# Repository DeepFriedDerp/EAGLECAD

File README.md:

# EAGLECAD
a place for my eagle files

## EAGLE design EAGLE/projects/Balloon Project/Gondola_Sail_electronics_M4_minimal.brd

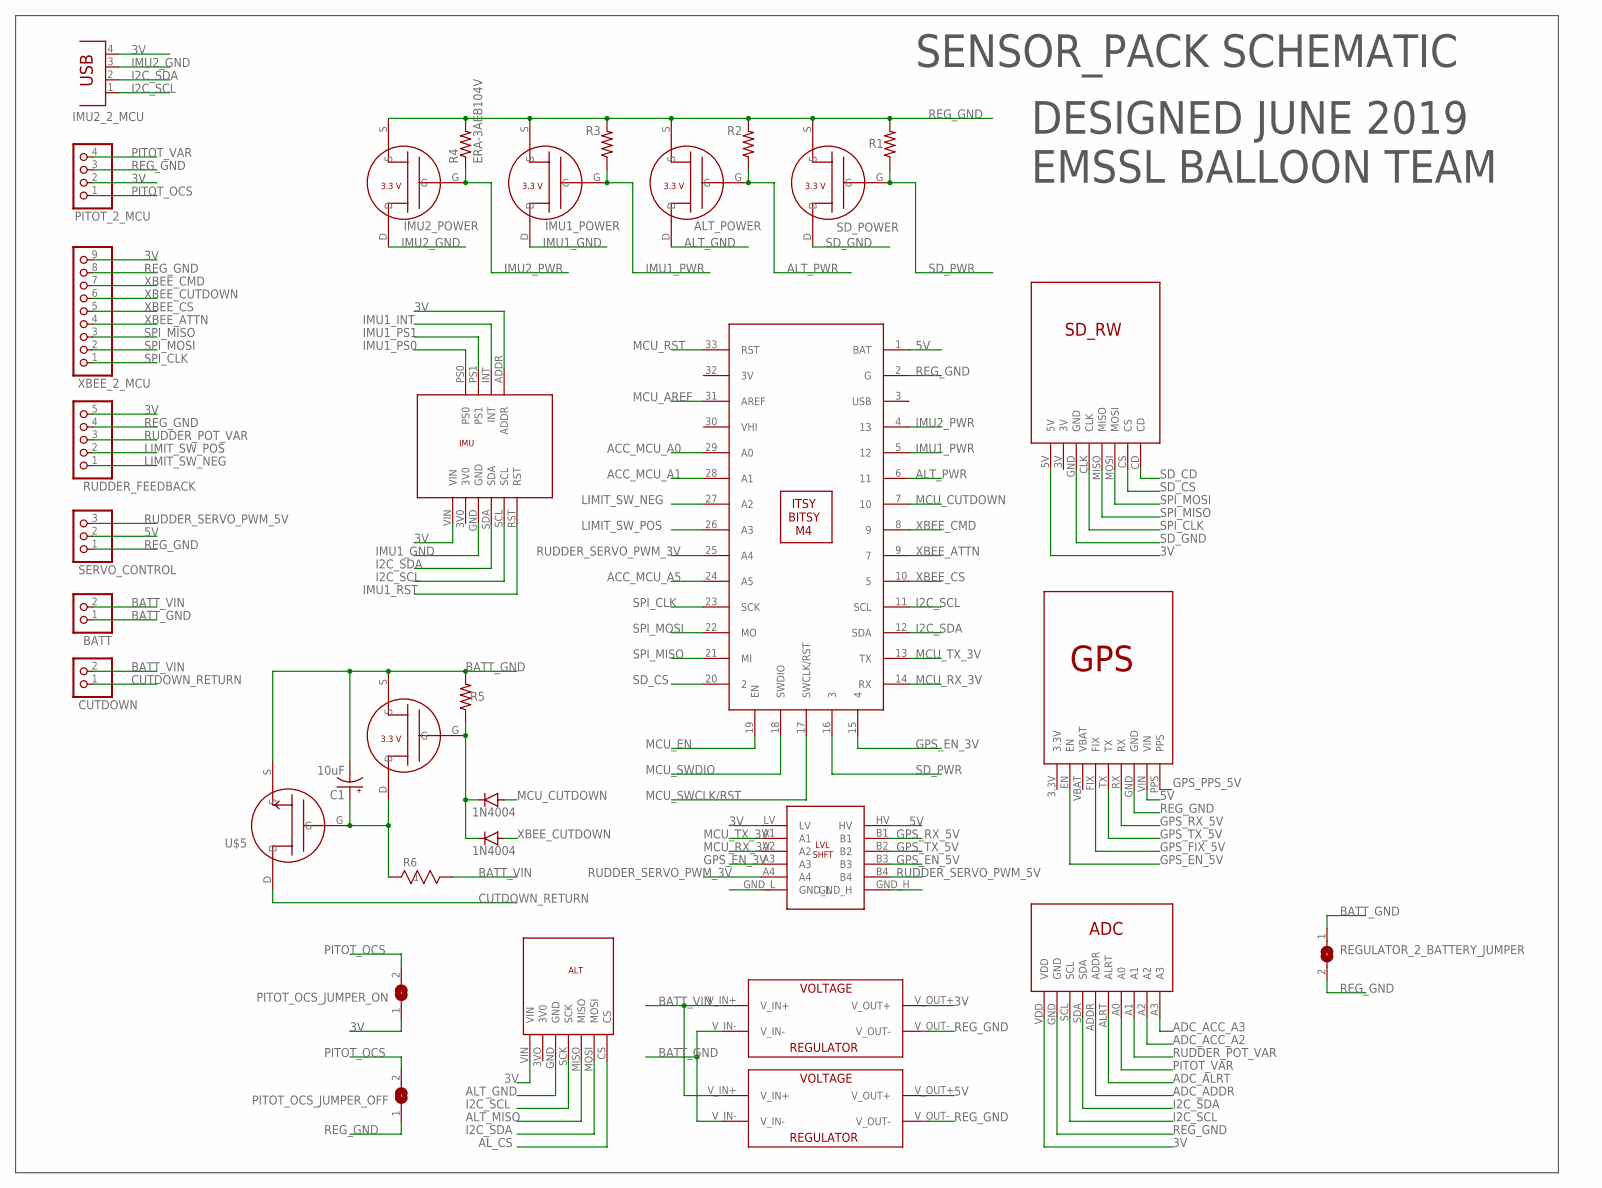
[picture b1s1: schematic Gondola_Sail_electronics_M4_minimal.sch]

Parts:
3V_REG, 5V_REG: 3V/5V_REGULATOR; 5V/3V_REGULATOR
ALT_POWER: 3.3V_NCH_FET; 3.3VTRANSISTOR
BATT: PINHD-1X2/90; 1X02/90
C1: 10uF; CPOL-RADIAL-2.5MM-5MM
CUTDOWN: PINHD-1X2/90; 1X02/90
D1, D2: 1N4004; DO41-10
IMU1: BNO055
IMU1_POWER, IMU2_POWER: 3.3V_NCH_FET; 3.3VTRANSISTOR
IMU2_2_MCU: PN87520
PITOT_2_MCU: PINHD-1X4/90; 1X04/90
PITOT_OCS_JUMPER_OFF: SJ
PITOT_OCS_JUMPER_ON: SJ
R1, R2, R3, R4, R5: ERA-3AEB104V; RESC1608X55
R6: RR0816P-103-D; RES_0816
REGULATOR_2_BATTERY_JUMPER: SJW
RUDDER_FEEDBACK: PINHD-1X5/90; 1X05/90
SD_POWER, SD_POWER1: 3.3V_NCH_FET; 3.3VTRANSISTOR
SERVO_CONTROL: PINHD-1X3/90; 1X03/90
U$1: ADAFRUIT_GPS
U$2: ADAFRUI_SD_RW; ADAFRUIT_SD_RW
U$3: ADS1115
U$4: BME280
U$5: CUTDOWN_POWER_TRANSISTOR; T03B
U$6: BSS138_LVLSHIFT; BSS138_LEVELSHIFT
U$8: ITSY_BITSY_M4
XBEE_2_MCU: PINHD-1X9/90; 1X09/90

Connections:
3V: 3V_REG.V_OUT+, IMU1.ADDR, IMU1.VIN, IMU2_2_MCU.4, PITOT_2_MCU.2, PITOT_OCS_JUMPER_ON.1, RUDDER_FEEDBACK.5, U$2.5V, U$3.VDD, U$4.VIN, U$6.LV, XBEE_2_MCU.9
5V: 5V_REG.V_OUT+, SERVO_CONTROL.2, U$1.VIN, U$6.HV, U$8.1 (BAT)
ACC_MCU_A0: U$8.29 (A0)
ACC_MCU_A1: U$8.28 (A1)
ACC_MCU_A5: U$8.24 (A5)
ADC_ACC_A2: U$3.A2
ADC_ACC_A3: U$3.A3
ADC_ADDR: U$3.ADDR
ADC_ALRT: U$3.ALRT
ALT_GND: ALT_POWER.D, U$4.GND
ALT_MISO: U$4.MISO
ALT_PWR: ALT_POWER.G, R2.1, U$8.6 (11)
AL_CS: U$4.CS
BATT_GND: 3V_REG.V_IN-, 5V_REG.V_IN-, BATT.1, C1.2 (-), R5.2, REGULATOR_2_BATTERY_JUMPER.1, SD_POWER1.S, U$5.S
BATT_VIN: 3V_REG.V_IN+, 5V_REG.V_IN+, BATT.2, CUTDOWN.2, R6.2
CUTDOWN: D1.C, D2.C, R5.1, SD_POWER1.G
CUTDOWN_RETURN: CUTDOWN.1, U$5.D
GPS_EN_3V: U$6.A3, U$8.15 (4)
GPS_EN_5V: U$1.EN, U$6.B3
GPS_FIX_5V: U$1.FIX
GPS_PPS_5V: U$1.PPS
GPS_RX_5V: U$1.RX, U$6.B1
GPS_TX_5V: U$1.TX, U$6.B2
I2C_SCL: IMU1.SCL, IMU2_2_MCU.1, U$3.SCL, U$4.SCK, U$8.11 (SCL)
I2C_SDA: IMU1.SDA, IMU2_2_MCU.2, U$3.SDA, U$4.MOSI, U$8.12 (SDA)
IMU1_GND: IMU1.GND, IMU1_POWER.D
IMU1_INT: IMU1.INT
IMU1_PS0: IMU1.PS0
IMU1_PS1: IMU1.PS1
IMU1_PWR: IMU1_POWER.G, R3.1, U$8.5 (12)
IMU1_RST: IMU1.RST
IMU2_GND: IMU2_2_MCU.3, IMU2_POWER.D
IMU2_PWR: IMU2_POWER.G, R4.1, U$8.4 (13)
LIMIT_SW_NEG: RUDDER_FEEDBACK.1, U$8.27 (A2)
LIMIT_SW_POS: RUDDER_FEEDBACK.2, U$8.26 (A3)
MCU_AREF: U$8.31 (AREF)
MCU_CUTDOWN: D1.A, U$8.7 (10)
MCU_EN: U$8.19 (EN)
MCU_RST: U$8.33 (RST)
MCU_RX_3V: U$6.A2, U$8.14 (RX)
MCU_SWCLK/RST: U$8.17 (SWCLK/RST)
MCU_SWDIO: U$8.18 (SWDIO)
MCU_TX_3V: U$6.A1, U$8.13 (TX)
unnamed: C1.1 (+), R6.1, SD_POWER1.D, U$5.G
PITOT_OCS: PITOT_2_MCU.1, PITOT_OCS_JUMPER_OFF.2, PITOT_OCS_JUMPER_ON.2
PITOT_VAR: PITOT_2_MCU.4, U$3.A0
REG_GND: 3V_REG.V_OUT-, 5V_REG.V_OUT-, ALT_POWER.S, IMU1_POWER.S, IMU2_POWER.S, PITOT_2_MCU.3, PITOT_OCS_JUMPER_OFF.1, R1.2, R2.2, R3.2, R4.2, REGULATOR_2_BATTERY_JUMPER.2, RUDDER_FEEDBACK.4, SD_POWER.S, SERVO_CONTROL.1, U$1.GND, U$3.GND, U$8.2 (G), XBEE_2_MCU.8
RUDDER_POT_VAR: RUDDER_FEEDBACK.3, U$3.A1
RUDDER_SERVO_PWM_3V: U$6.A4, U$8.25 (A4)
RUDDER_SERVO_PWM_5V: SERVO_CONTROL.3, U$6.B4
SD_CD: U$2.CD
SD_CS: U$2.CS, U$8.20 (2)
SD_GND: SD_POWER.D, U$2.GND
SD_PWR: R1.1, SD_POWER.G, U$8.16 (3)
SPI_CLK: U$2.CLK, U$8.23 (SCK), XBEE_2_MCU.1
SPI_MISO: U$2.MISO, U$8.21 (MI), XBEE_2_MCU.3
SPI_MOSI: U$2.MOSI, U$8.22 (MO), XBEE_2_MCU.2
XBEE_ATTN: U$8.9 (7), XBEE_2_MCU.4
XBEE_CMD: U$8.8 (9), XBEE_2_MCU.7
XBEE_CS: U$8.10 (5), XBEE_2_MCU.5
XBEE_CUTDOWN: D2.A, XBEE_2_MCU.6

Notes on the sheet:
SENSOR_PACK SCHEMATIC
DESIGNED JUNE 2019 EMSSL BALLOON TEAM

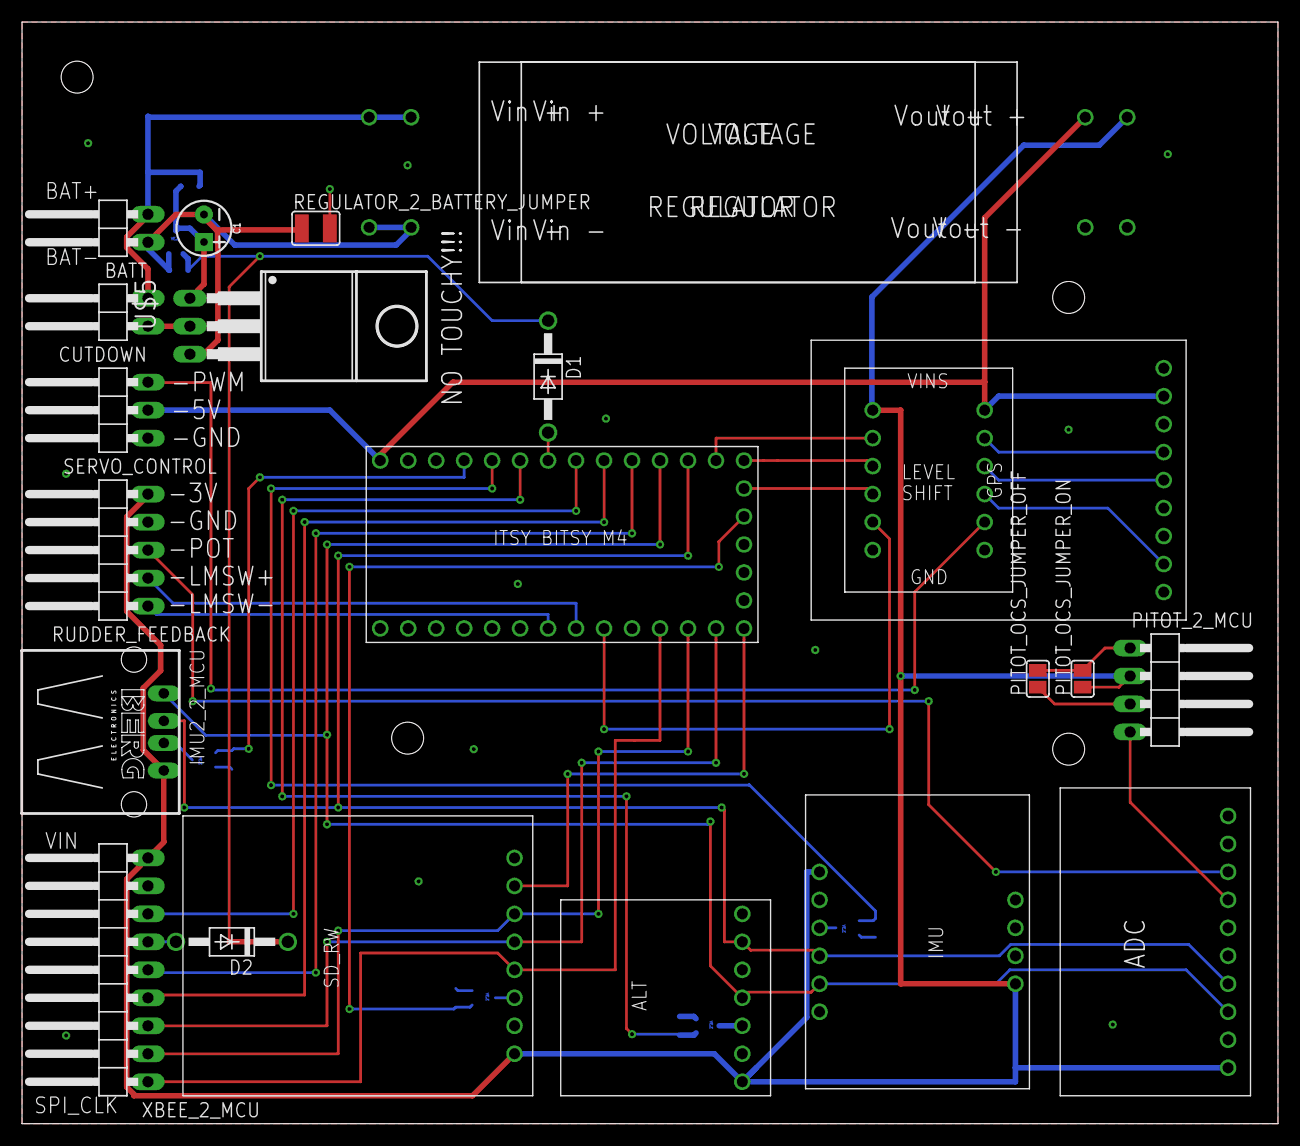
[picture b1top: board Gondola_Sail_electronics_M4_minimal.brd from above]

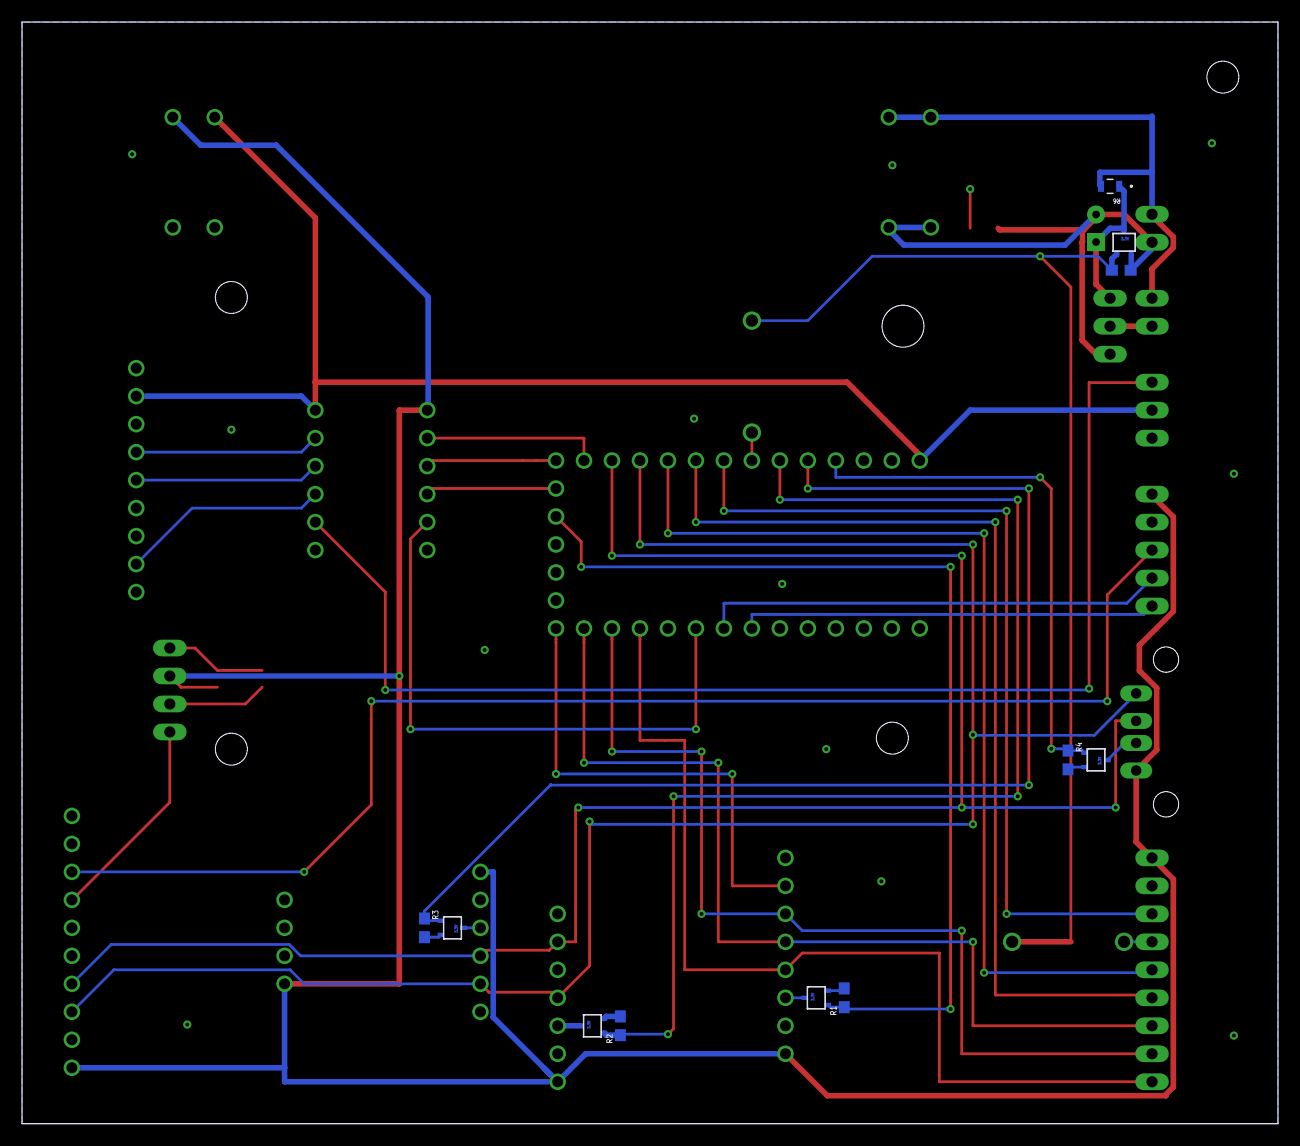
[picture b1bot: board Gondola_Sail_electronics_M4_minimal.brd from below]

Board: 2 copper layers, 114.0 x 100.0 mm, 34 parts (11 on the bottom side), 40 nets.

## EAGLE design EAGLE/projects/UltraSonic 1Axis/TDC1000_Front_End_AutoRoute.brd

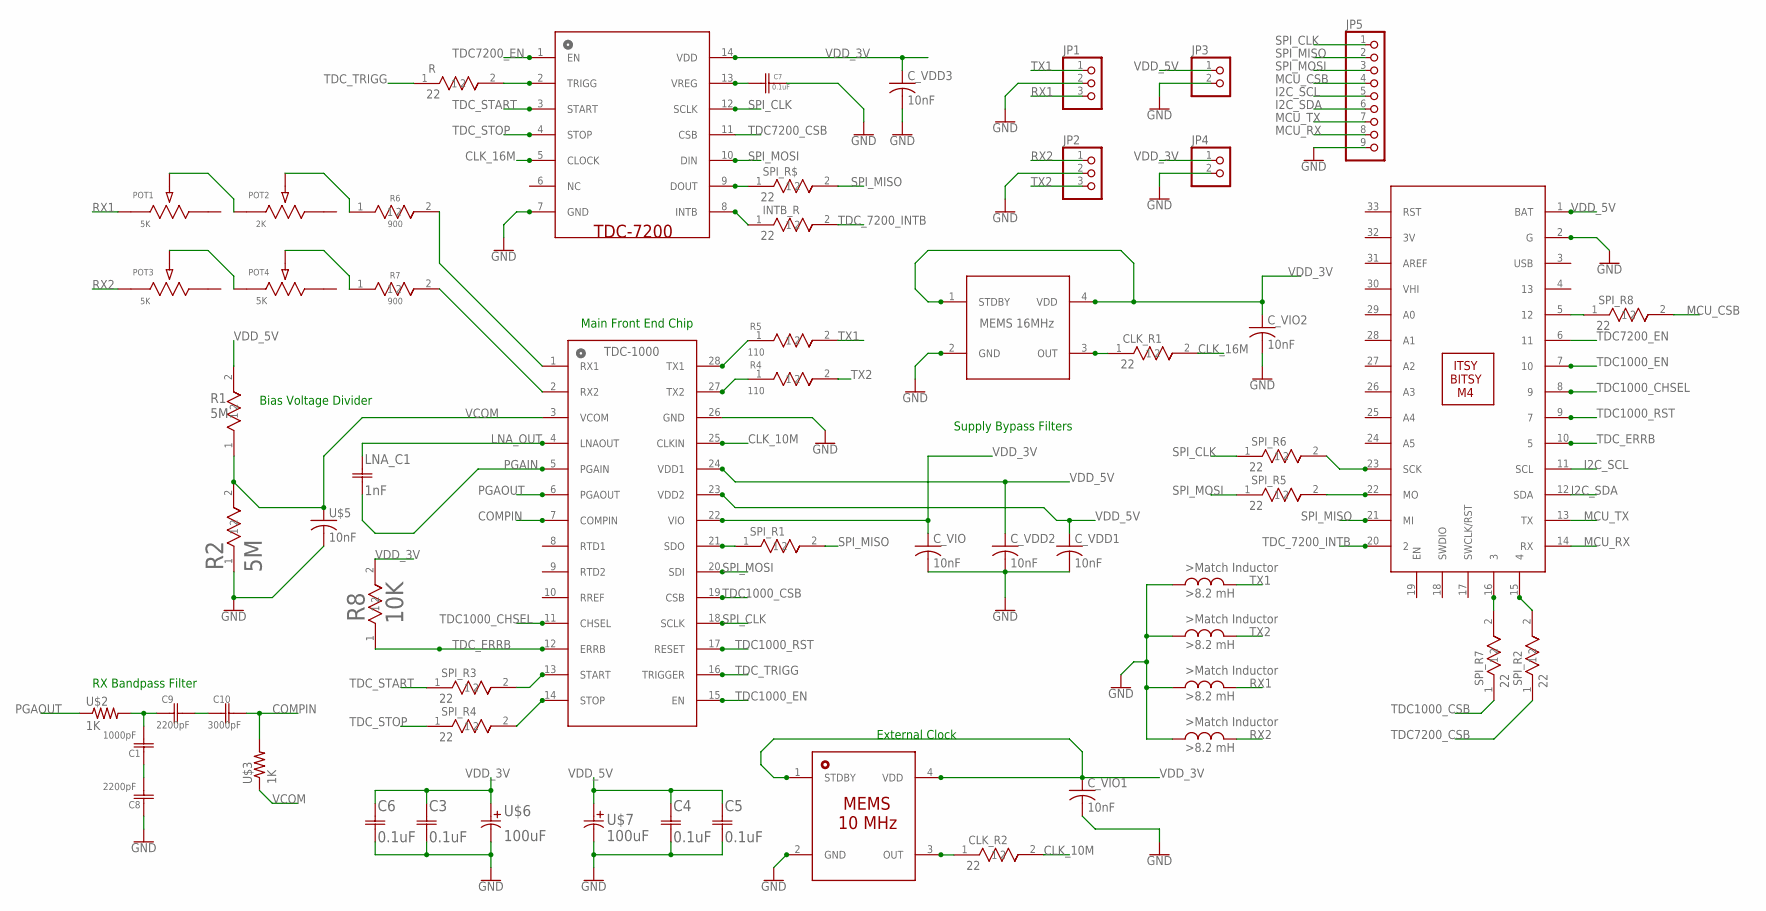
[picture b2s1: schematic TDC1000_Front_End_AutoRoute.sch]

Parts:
C1: 1000pF; 0603
C3, C4, C5, C6, C7: 0.1uF; 0603
C8, C9: 2200pF; 0603
C10: 3000pF; 0603
CLK_R1, CLK_R2: 22; MMB0207
C_VDD1, C_VDD2, C_VDD3: 10nF; CL05B103KB5NNNC
C_VIO, C_VIO1, C_VIO2: 10nF; CL05B103KB5NNNC
INTB_R: 22; MMB0207
JP1, JP2: PINHD-1X3/90; 1X03/90
JP3, JP4: PINHD-1X2/90; 1X02/90
JP5: PINHD-1X9; 1X09
LNA_C1: 1nF; 0603
POT1, POT3, POT4: 5K; POT_3362P
POT2: 2K; POT_3362P
R: 22; MMB0207
R1, R2: 5M; 1206
R4, R5: 110; RES_1220
R6, R7: 900; 1206
R8: 10K; RES_0816
SPI_R1, SPI_R2, SPI_R3, SPI_R4, SPI_R5, SPI_R6, SPI_R7, SPI_R8: 22; MMB0207
SPI_R$: 22; MMB0207
U$1: TDC1000_TSSOP
U$2, U$3: 1K; ROHM_ESR03
U$4: DSC1001CL5-010.0000_2.5X10MHZ_2.5X3.2MM; DSC1001CL5-010.0000_2.5X3.2MM
U$5: 10nF; CL05B103KB5NNNC
U$6, U$7: 100uF; UKL1E101KPDANATA_100UF
U$8: TDC7200_TSSOPTSSOP-14; TDC7200_TSSOP
U$9: DSC1001BL5-016.0000_5X3.2MM
U$10: ITSY_BITSY_M4
U$11, U$12, U$13, U$14: AIUR_16_8.2MH_INDUCTOR; AIUR-16_8MH_INDUCTOR

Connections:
CLK_10M: CLK_R2.2, U$1.25 (CLKIN)
CLK_16M: CLK_R1.2, U$8.5 (CLOCK)
COMPIN: C10.2, U$1.7 (COMPIN), U$3.P$2 (2)
GND: C3.1, C4.1, C5.1, C6.1, C7.2, C8.2, C_VDD1.2, C_VDD2.2, C_VDD3.2, C_VIO.2, C_VIO1.2, C_VIO2.2, JP1.2, JP2.2, JP3.2, JP4.2, JP5.9, R2.1, U$1.26 (GND), U$4.2 (GND), U$5.2, U$6.1, U$7.1, U$8.7 (GND), U$9.2 (GND), U$10.2 (G), U$11.1, U$12.1, U$13.1, U$14.1
I2C_SCL: JP5.5, U$10.11 (SCL)
I2C_SDA: JP5.6, U$10.12 (SDA)
LNA_OUT: LNA_C1.2, U$1.4 (LNAOUT)
MCU_CSB: JP5.4, SPI_R8.2
MCU_RX: JP5.8, U$10.14 (RX)
MCU_TX: JP5.7, U$10.13 (TX)
unnamed: SPI_R1.1, U$1.21 (SDO)
unnamed: SPI_R2.2, U$10.15 (4)
unnamed: R.2, U$8.2 (TRIGG)
unnamed: SPI_R3.2, U$1.13 (START)
unnamed: SPI_R8.1, U$10.5 (12)
unnamed: CLK_R2.1, U$4.3 (OUT)
unnamed: C1.1, C9.1, U$2.P$2 (2)
unnamed: R5.1, U$1.28 (TX1)
unnamed: C9.2, C10.1
unnamed: R4.1, U$1.27 (TX2)
unnamed: SPI_R4.2, U$1.14 (STOP)
unnamed: SPI_R$.1, U$8.9 (DOUT)
unnamed: INTB_R.1, U$8.8 (INTB)
unnamed: SPI_R6.2, U$10.23 (SCK)
unnamed: SPI_R5.2, U$10.22 (MO)
unnamed: CLK_R1.1, U$9.3 (OUT)
unnamed: C7.1, U$8.13 (VREG)
unnamed: SPI_R7.2, U$10.16 (3)
unnamed: POT4.2, R7.1
unnamed: POT3.2, POT4.1
unnamed: R7.2, U$1.2 (RX2)
unnamed: R6.2, U$1.1 (RX1)
unnamed: POT1.2, POT2.1
unnamed: POT2.2, R6.1
unnamed: C1.2, C8.1
PGAIN: LNA_C1.1, U$1.5 (PGAIN)
PGAOUT: U$1.6 (PGAOUT), U$2.P$1 (1)
RX1: JP1.3, POT1.1, U$14.2
RX2: JP2.1, POT3.1, U$13.2
SPI_CLK: JP5.1, SPI_R6.1, U$1.18 (SCLK), U$8.12 (SCLK)
SPI_MISO: JP5.2, SPI_R1.2, SPI_R$.2, U$10.21 (MI)
SPI_MOSI: JP5.3, SPI_R5.1, U$1.20 (SDI), U$8.10 (DIN)
TDC1000_CHSEL: U$1.11 (CHSEL), U$10.8 (9)
TDC1000_CSB: SPI_R7.1, U$1.19 (CSB)
TDC1000_EN: U$1.15 (EN), U$10.7 (10)
TDC1000_RST: U$1.17 (RESET), U$10.9 (7)
TDC7200_CSB: SPI_R2.1, U$8.11 (CSB)
TDC7200_EN: U$8.1 (EN), U$10.6 (11)
TDC_7200_INTB: INTB_R.2, U$10.20 (2)
TDC_ERRB: R8.1, U$1.12 (ERRB), U$10.10 (5)
TDC_START: SPI_R3.1, U$8.3 (START)
TDC_STOP: SPI_R4.1, U$8.4 (STOP)
TDC_TRIGG: R.1, U$1.16 (TRIGGER)
TX1: JP1.1, R5.2, U$12.2
TX2: JP2.3, R4.2, U$11.2
VCOM: R1.1, R2.2, U$1.3 (VCOM), U$3.P$1 (1), U$5.1
VDD_3V: C3.2, C6.2, C_VDD3.1, C_VIO.1, C_VIO1.1, C_VIO2.1, JP4.1, R8.2, U$1.22 (VIO), U$4.1 (STDBY), U$4.4 (VDD), U$6.2, U$8.14 (VDD), U$9.1 (STDBY), U$9.4 (VDD)
VDD_5V: C4.2, C5.2, C_VDD1.1, C_VDD2.1, JP3.1, R1.2, U$1.23 (VDD2), U$1.24 (VDD1), U$7.2, U$10.1 (BAT)

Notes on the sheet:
External Clock
Main Front End Chip
RX Bandpass Filter
Bias Voltage Divider
Supply Bypass Filters

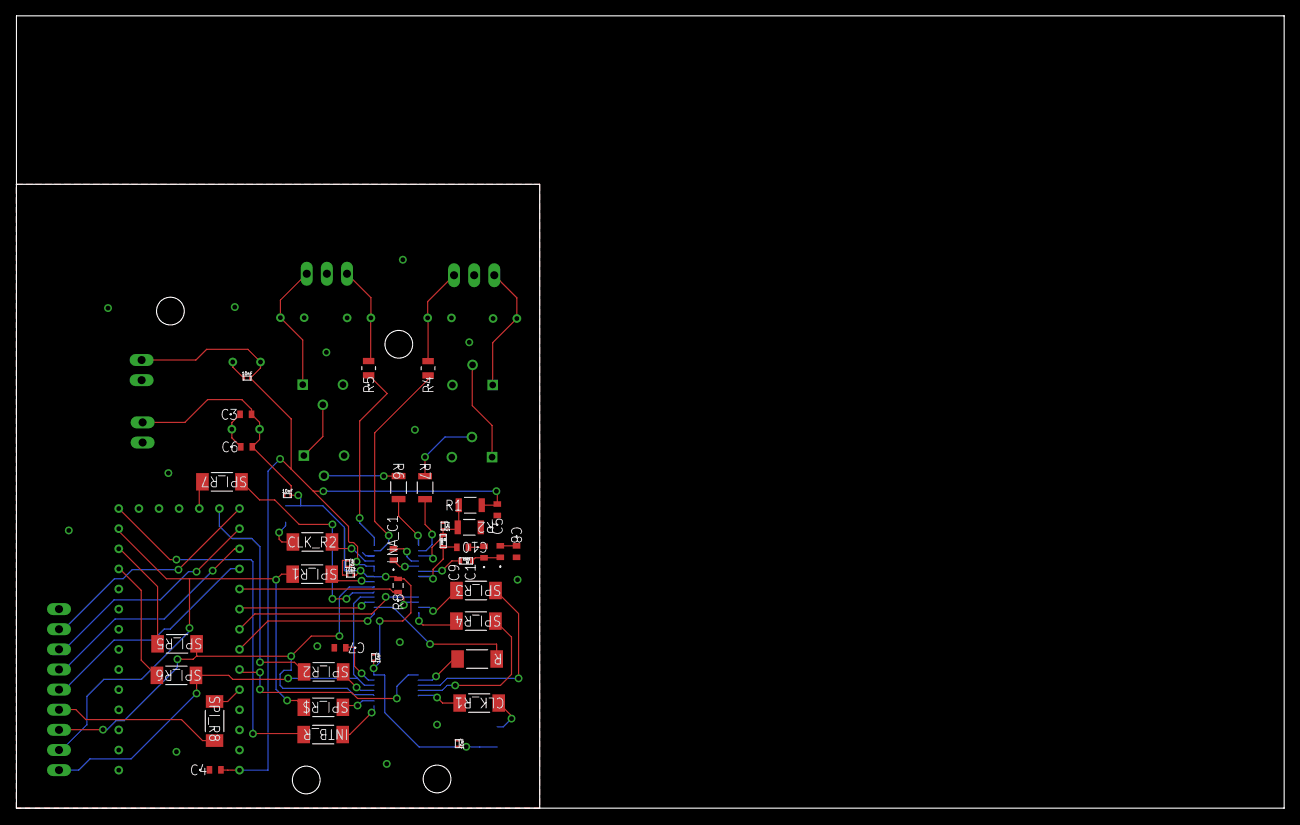
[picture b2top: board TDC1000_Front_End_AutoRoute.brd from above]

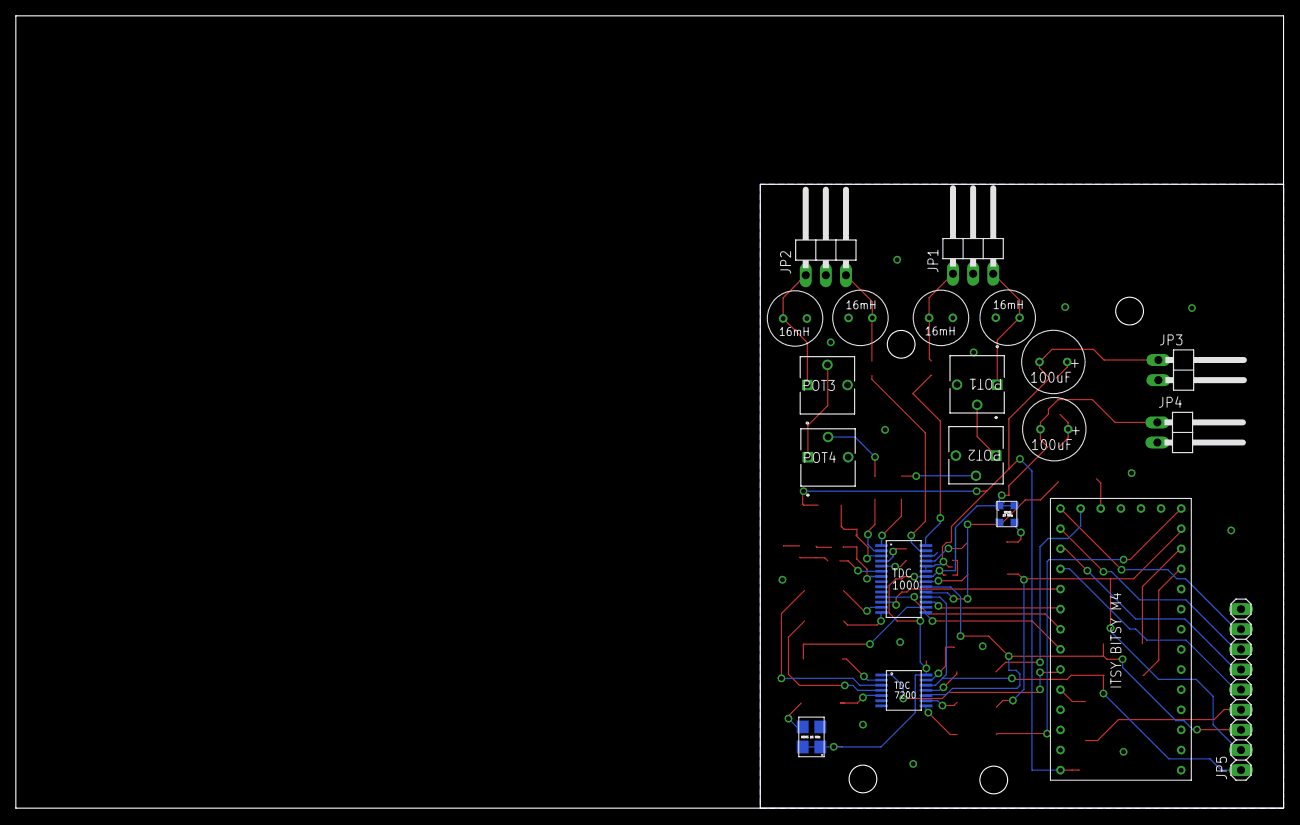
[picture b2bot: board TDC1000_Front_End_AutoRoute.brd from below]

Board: 2 copper layers, 159.9 x 99.9 mm, 59 parts (20 on the bottom side), 58 nets.

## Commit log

2019-04-26 Initial clone/commit
    everything I've got up until now...
2019-06-17 Create Gondola_Sail_electronics_M4.sch
    starting the PCB
2019-06-19 added library files
    added library items for the upcoming telemetry pcb
2019-06-19 DERP
2019-06-20 building pcb schematic
2019-06-20 building sensorpack and new breakouts
    added accessory connections to sensor board, address jumpers, etc.
    built remote imu breakout and xbee breakout.
2019-06-20 update libraries
2019-06-21 planning out pcb
    placing parts and routing traces
    added cutdown assembly
2019-06-21 added minimal sensorpack
    full sensor pack has too many breakout pins, need to trim down the size of the board. starting routing traces
2019-06-21 minimal telemetry/sensor board complete
2019-06-22 gerber files generated
2019-06-24 optimized board layout - finished
    -minimized vias
    -optimized some routes
    -added silkscreen to xbee
    -ERC and DRC checks out for all boards
    -ready for ordering
2019-06-24 finished up before orders made
2019-07-07 created mirrored gerbers
    to help with voltera alignment for solder paste dispensing

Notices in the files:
parts and their libraries:
SparkFun-Capacitors: Licensing: Creative Commons ShareAlike 4.0 International - https://creativecommons.org/licenses/by-sa/4.0
